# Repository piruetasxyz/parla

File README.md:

# parla

Un proyecto de piruetas, 2026.

## Módulos

Cada módulo tiene su propia carpeta con un proyecto de KiCad, organizado por versión y revisión (por ejemplo `parla-linea/parla-linea-v-0-rev-a/`).

|                      | parla-linea                            | parla-eurorack                           | parla-guitarra        | parla-estereo          |
| -------------------- | -------------------------------------- | ---------------------------------------- | --------------------- | ---------------------- |
| formato              | standalone                             | eurorack                                 | standalone            | standalone             |
| entrada alimentación | batería 9V                             | por definir                              | batería 9V            | por definir            |
| chip                 | PAM8403                                | por definir                              | LM386                 | PAM8403                |
| interfaz             | 1x pote                                | 2x potes                                 | 1x pote               | 2x potes               |
| entrada señal        | 1x línea TRS                           | 1x eurorack                              | 1x guitarra           | 1x línea TRS           |
| conector entrada     | TRS 1/8"                               | TS 1/8"                                  | TS 1/4"               | TRS 1/8"               |
| salidas              | 1x parlante, 1x línea                  | 1x parlante, 1x eurorack                 | 1x parlante           | 2x parlantes           |
| conector salida      | parlante: por definir, línea: TRS 1/8" | parlante: por definir, eurorack: TS 1/8" | parlante: por definir | parlantes: por definir |

### Extensores

|                  | parla-linea-extensor  | parla-eurorack-extensor |
| ---------------- | --------------------- | ----------------------- |
| formato          | standalone            | eurorack                |
| alimentación     | ninguna               | por definir             |
| chip             | ninguno               | por definir             |
| interfaz         | —                     | —                       |
| entradas         | 1x línea              | 1x eurorack             |
| conector entrada | TRS 1/8"              | TS 1/8"                 |
| salidas          | 1x parlante           | 1x parlante             |
| conector salida  | parlante: por definir | parlante: por definir   |

## Documentación

Esquemáticos, placas y bill of materials (BOM) de cada módulo, generados automáticamente: [docs](./docs/README.md).

### Agregar las bibliotecas de parla-linea a KiCad

Las bibliotecas generadas están en `parla-linea/parla-linea-v-0-rev-a/bibliotecas/`.
Para que KiCad las encuentre, abre primero el proyecto
`parla-linea/parla-linea-v-0-rev-a/parla-linea-v-0-rev-a.kicad_pro` y agrégalas
como bibliotecas específicas de ese proyecto:

1. En KiCad, abre **Preferencias → Administrar bibliotecas de símbolos…**.
2. En **Bibliotecas específicas del proyecto**, pulsa **Añadir biblioteca existente**
   y selecciona
   `parla-linea/parla-linea-v-0-rev-a/bibliotecas/parla-linea-v-0-rev-a.kicad_sym`.
3. Abre **Preferencias → Administrar bibliotecas de huellas…**.
4. En **Bibliotecas específicas del proyecto**, pulsa **Añadir biblioteca existente**
   y selecciona la carpeta
   `parla-linea/parla-linea-v-0-rev-a/bibliotecas/parla-linea-v-0-rev-a.pretty`
   (no un archivo dentro de ella).
5. Confirma los cambios. Las bibliotecas deberían aparecer en los selectores de
   símbolos y huellas del proyecto.

Agrégalas como bibliotecas **específicas del proyecto**, no globales, para que las
rutas queden asociadas a este proyecto. Los modelos 3D están en la carpeta hermana
`parla-linea/parla-linea-v-0-rev-a/bibliotecas/parla-linea-v-0-rev-a.3dshapes/`;
las huellas los referencian desde ahí, así que no hace falta registrarlos como
biblioteca aparte. Si el proyecto ya estaba abierto mientras agregabas las
bibliotecas, cierra y vuelve a abrir el proyecto.

### Enlaces por módulo

- parla-linea: [carpeta](https://github.com/piruetasxyz/parla/tree/main/parla-linea), [docs](./docs/parla-linea.md)
- parla-eurorack: [carpeta](https://github.com/piruetasxyz/parla/tree/main/parla-eurorack), [docs](./docs/parla-eurorack.md)
- parla-guitarra: [carpeta](https://github.com/piruetasxyz/parla/tree/main/parla-guitarra), [docs](./docs/parla-guitarra.md)
- parla-estereo: [carpeta](https://github.com/piruetasxyz/parla/tree/main/parla-estereo), [docs](./docs/parla-estereo.md)
- parla-linea-extensor: [carpeta](https://github.com/piruetasxyz/parla/tree/main/parla-linea-extensor), [docs](./docs/parla-linea-extensor.md)
- parla-eurorack-extensor: [carpeta](https://github.com/piruetasxyz/parla/tree/main/parla-eurorack-extensor), [docs](./docs/parla-eurorack-extensor.md)

## Versiones antiguas

Hicimos versiones preliminares que están en la carpeta [versiones-antiguas](https://github.com/piruetasxyz/parla/tree/main/versiones-antiguas):

- `parla-v0-borrador`: primeros experimentos de esquemáticos (enero-febrero 2026).
- `parla-v0-revA`: versión producida con SMD en JLCPCB.
- `parla-v0-revB`: revisión de la placa con algunos cambios (junio 2026), junto a sus gerbers y archivos de PCBA.
- `graficas`: logos y gráficas usadas en las placas.

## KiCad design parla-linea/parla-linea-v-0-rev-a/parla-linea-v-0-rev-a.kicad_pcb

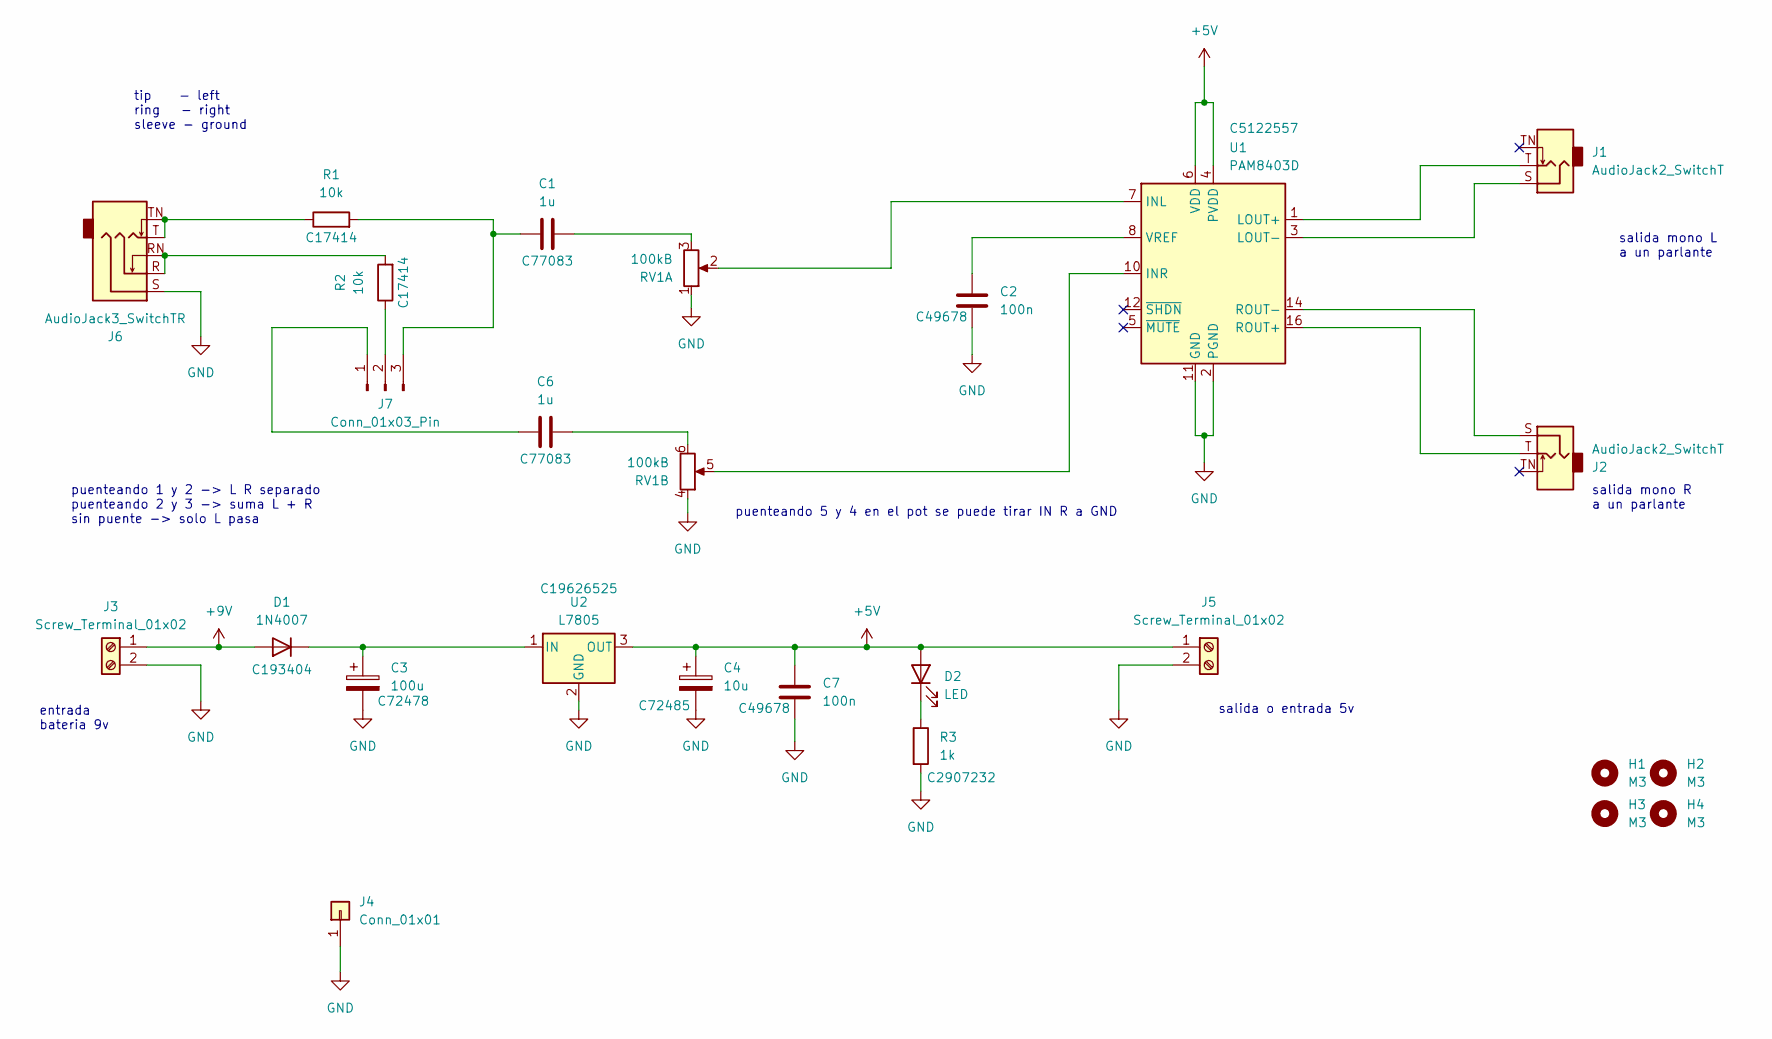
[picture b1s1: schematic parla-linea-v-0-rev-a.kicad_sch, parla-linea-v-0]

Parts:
C1, C6: 1u; C0805; LCSC C77083
C2, C7: 100n; C0805; LCSC C49678
C3: 100u; CAP-SMD_BD6.3-L6.6-W6.6-LS7.6-FD; LCSC C72478
C4: 10u; CAP-SMD_BD4.0-L4.3-W4.3-FD; LCSC C72485
D1: 1N4007; SOD-323_L1.8-W1.3-LS2.5-RD; LCSC C193404
D2: LED; LED3mm
H1, H2, H3, H4: M3; MountingHole_3.2mm_M3
J1, J2: AudioJack2_SwitchT; Jack_3.5mm_QingPu_WQP-PJ398SM_Vertical_CircularHoles
J3, J5: Screw_Terminal_01x02; TerminalBlock_MaiXu_MX126-5.0-02P_1x02_P5.00mm
J4: Conn_01x01; SolderWire-0.25sqmm_1x01_D0.65mm_OD1.7mm
J6: AudioJack3_SwitchTR; Jack_3.5mm_CUI_SJ1-3525N_Horizontal
J7: Conn_01x03_Pin; PinHeader_1x03_P2.54mm_Vertical
R1, R2: 10k; R0805; LCSC C17414
R3: 1k; R0805; LCSC C2907232
RV1: 100kB; Potentiometer_Alps_RK163_Dual_Horizontal
U1: PAM8403D; SOP-16_L10.0-W3.9-P1.27-LS6.0-BL; LCSC C5122557
U2: L7805; TO-252-2_L6.6-W6.1-P4.57-LS9.9-BR-CW; LCSC C19626525

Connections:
+5V: C4.1, C7.1, D2.2 (A), J5.1, U1.4 (PVDD), U1.6 (VDD), U1.13 (PVDD), U2.3 (OUT)
+9V: D1.2 (A), J3.1
GND: C2.2, C3.2, C4.2, C7.2, J3.2, J4.1 (Pin_1_1), J5.2, J6.S, R3.2, RV1.1, RV1.4, U1.2 (PGND), U1.11 (GND), U1.15 (PGND), U2.2 (GND)
unnamed: C1.2, RV1.3
unnamed: C6.2, RV1.6
unnamed: C3.1, D1.1 (K), U2.1 (IN)
unnamed: D2.1 (K), R3.1
unnamed: J6.R, J6.RN, R2.2
unnamed: J6.T, J6.TN, R1.1
unnamed: C6.1, J7.1
unnamed: J7.2, R2.1
unnamed: C1.1, J7.3, R1.2
unnamed: RV1.2, U1.7 (INL)
unnamed: RV1.5, U1.10 (INR)
unnamed: J1.T, U1.1 (LOUT+)
unnamed: J1.S, U1.3 (LOUT-)
unnamed: J2.T, U1.16 (ROUT+)
unnamed: J2.S, U1.14 (ROUT-)
unnamed: C2.1, U1.8 (VREF)

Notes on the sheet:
salida mono L a un parlante
tip - left ring - right sleeve - ground
salida mono R a un parlante
puenteando 1 y 2 -> L R separado puenteando 2 y 3 -> suma L + R sin puente -> solo L pasa
entrada bateria 9v
puenteando 5 y 4 en el pot se puede tirar IN R a GND
salida o entrada 5v

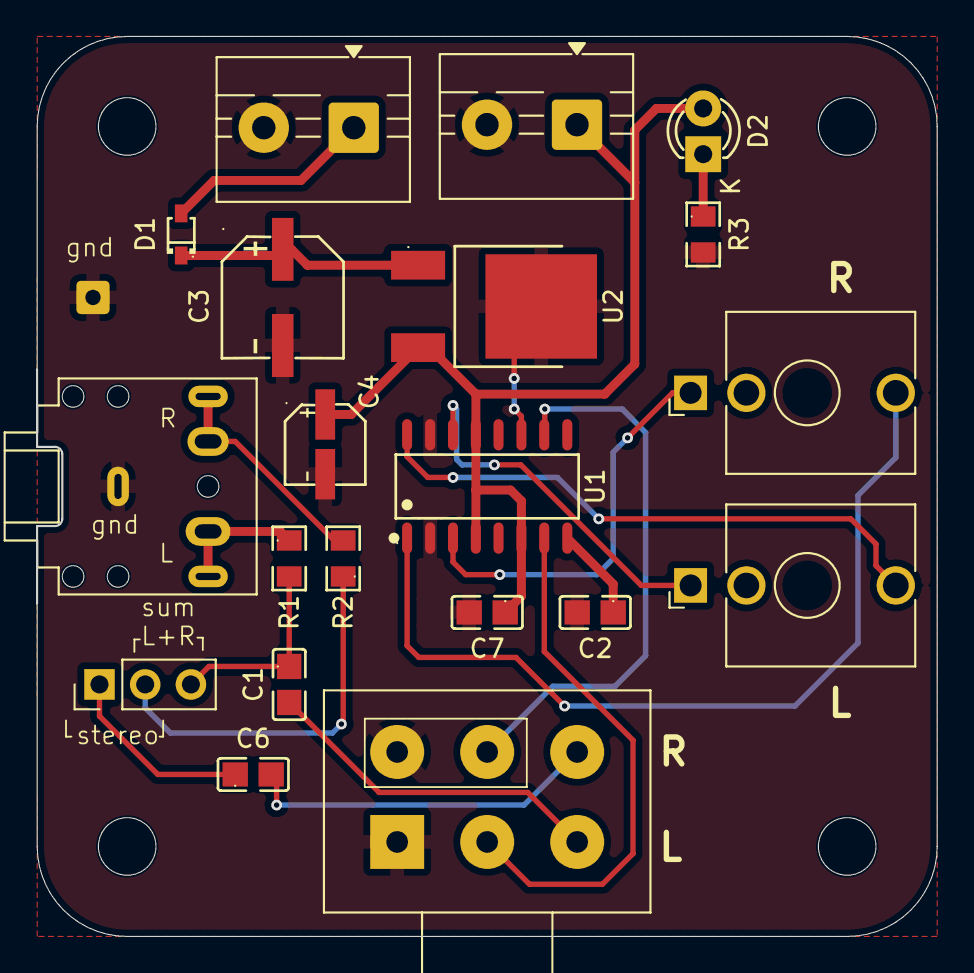
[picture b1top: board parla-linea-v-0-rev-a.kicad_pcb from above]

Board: 2 copper layers, 50.0 x 49.9 mm, 25 parts (0 on the bottom side), 19 nets.

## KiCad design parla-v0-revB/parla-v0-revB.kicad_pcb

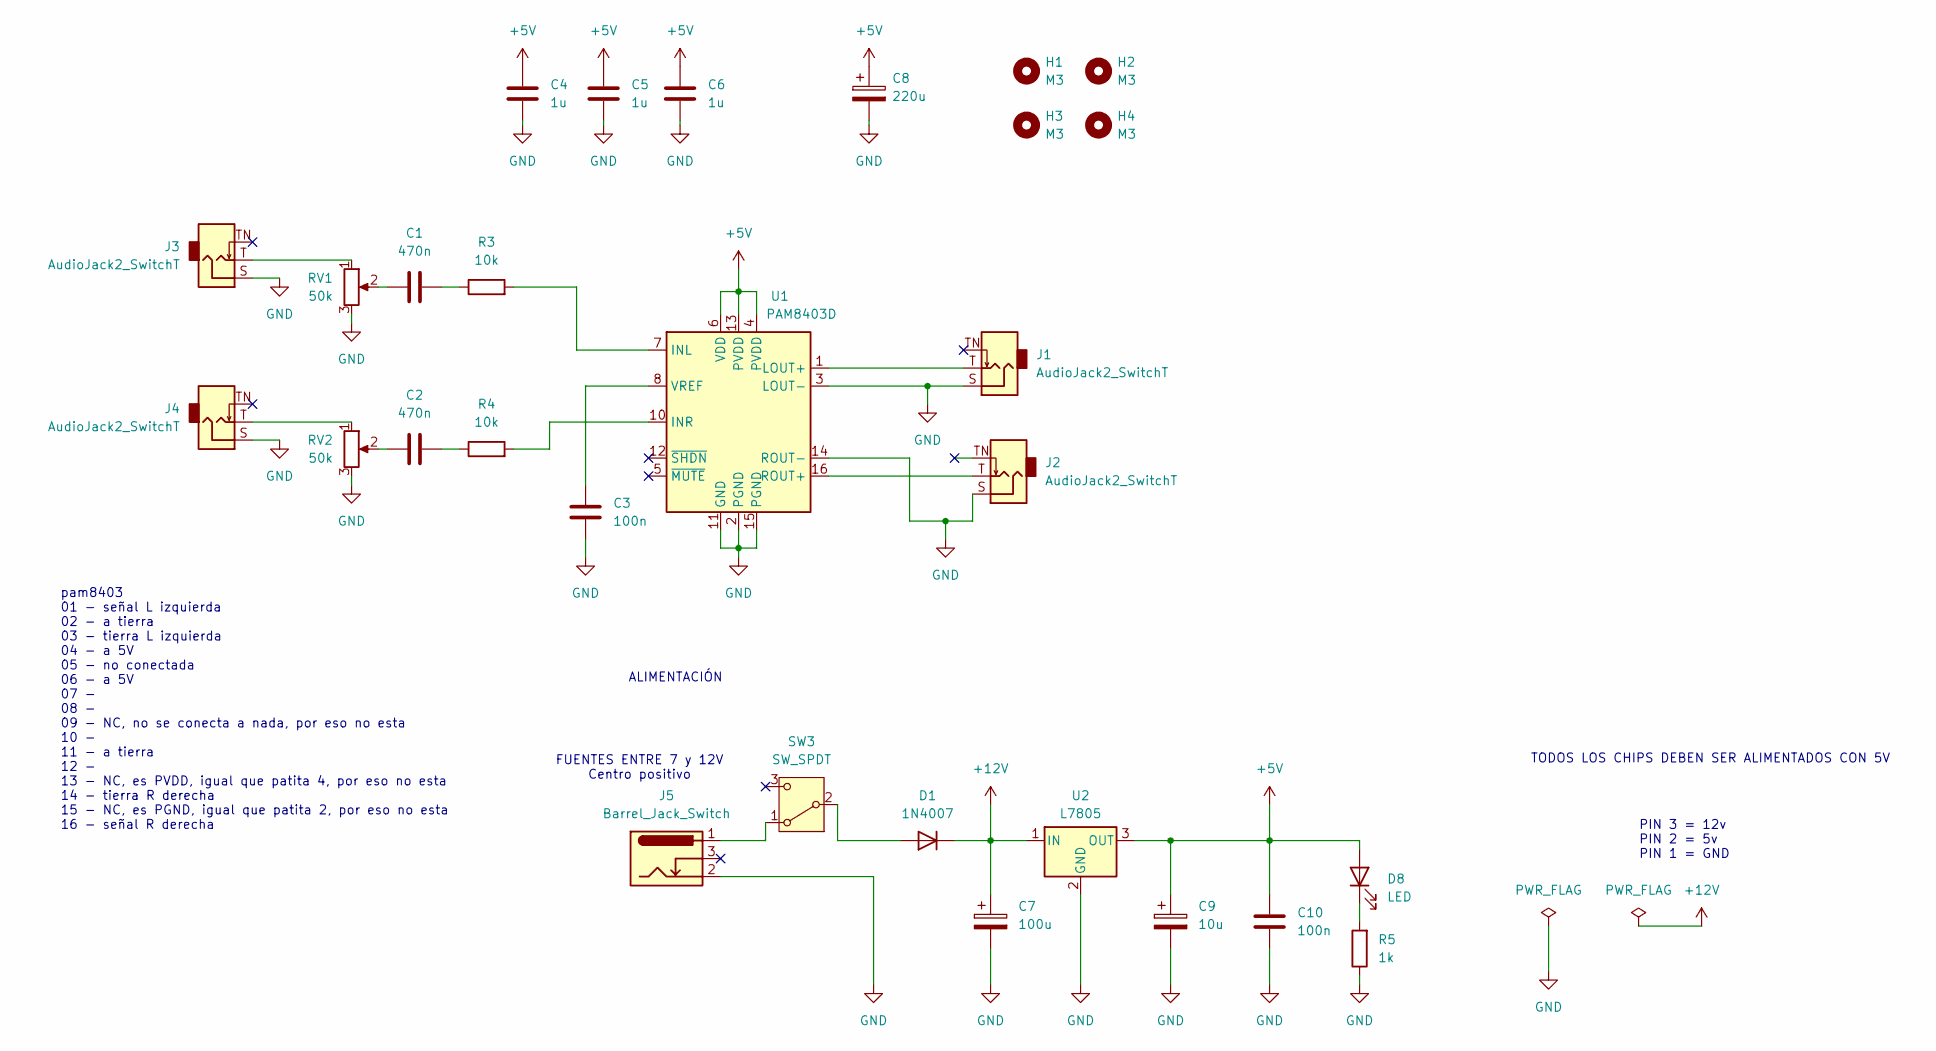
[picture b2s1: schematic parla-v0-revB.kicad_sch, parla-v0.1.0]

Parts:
C1, C2: 470n; C_Elec_4x5.4; LCSC C2895732
C3, C10: 100n; C_0805_2012Metric_Pad1.18x1.45mm_HandSolder; LCSC C49678
C4, C5, C6: 1u; C_0805_2012Metric_Pad1.18x1.45mm_HandSolder; LCSC C77083
C7: 100u; CP_Elec_5x5.4; LCSC C3347
C8: 220u; CP_Elec_6.3x7.7; LCSC C3342
C9: 10u; CP_Elec_4x5.4; LCSC C3357
D1: 1N4007; D_SOD-323_HandSoldering; LCSC C193404
D8: LED; LED_D5.0mm
H1, H2, H3, H4: M3; MountingHole_3.2mm_M3
J1, J2, J3, J4: AudioJack2_SwitchT; PJ301M-12-T_TN_S
J5: Barrel_Jack_Switch; BarrelJack_Horizontal
R3, R4: 10k; R_0805_2012Metric_Pad1.20x1.40mm_HandSolder; LCSC C17414
R5: 1k; R_0805_2012Metric_Pad1.20x1.40mm_HandSolder; LCSC C2907232
RV1, RV2: 50k; Potentiometer_Bourns_PTV09A-1_Single_Vertical
SW3: SW_SPDT; spdt_ssd12d00g3
U1: PAM8403D; SOP-16_4.4x10.4mm_P1.27mm; LCSC C5122557
U2: L7805; TO-252-2; LCSC C19626525

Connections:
+5V: C4.2, C5.2, C6.2, C8.1, C9.1, C10.1, D8.2 (A), U1.4 (PVDD), U1.6 (VDD), U1.13 (PVDD), U2.3 (OUT)
+12V: C7.1, D1.1 (K), U2.1 (IN)
GND: C3.2, C4.1, C5.1, C6.1, C7.2, C8.2, C9.2, C10.2, J1.S, J2.S, J3.S, J4.S, J5.2, R5.1, RV1.3, RV2.3, U1.2 (PGND), U1.3 (LOUT-), U1.11 (GND), U1.14 (ROUT-), U1.15 (PGND), U2.2 (GND)
unnamed: C1.1, RV1.2
unnamed: C1.2, R3.1
unnamed: C2.1, RV2.2
unnamed: C2.2, R4.1
unnamed: D1.2 (A), SW3.2 (B)
unnamed: D8.1 (K), R5.2
unnamed: J3.T, RV1.1
unnamed: J4.T, RV2.1
unnamed: J5.1, SW3.1 (A)
unnamed: R3.2, U1.7 (INL)
unnamed: R4.2, U1.10 (INR)
unnamed: J1.T, U1.1 (LOUT+)
unnamed: J2.T, U1.16 (ROUT+)
unnamed: C3.1, U1.8 (VREF)

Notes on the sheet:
FUENTES ENTRE 7 y 12V Centro positivo
PIN 3 = 12v PIN 2 = 5v PIN 1 = GND
TODOS LOS CHIPS DEBEN SER ALIMENTADOS CON 5V
ALIMENTACIÓN
pam8403 01 - señal L izquierda 02 - a tierra 03 - tierra L izquierda 04 - a 5V 05 - no conectada 06 - a 5V 07 - 08 - 09 - NC, no se conecta a nada, por eso no esta 10 - 11 - a tierra 12 - 13 - NC, es PVDD, igual que patita 4, por eso no esta 14 - tierra R derecha 15 - NC, es PGND, igual que patita 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

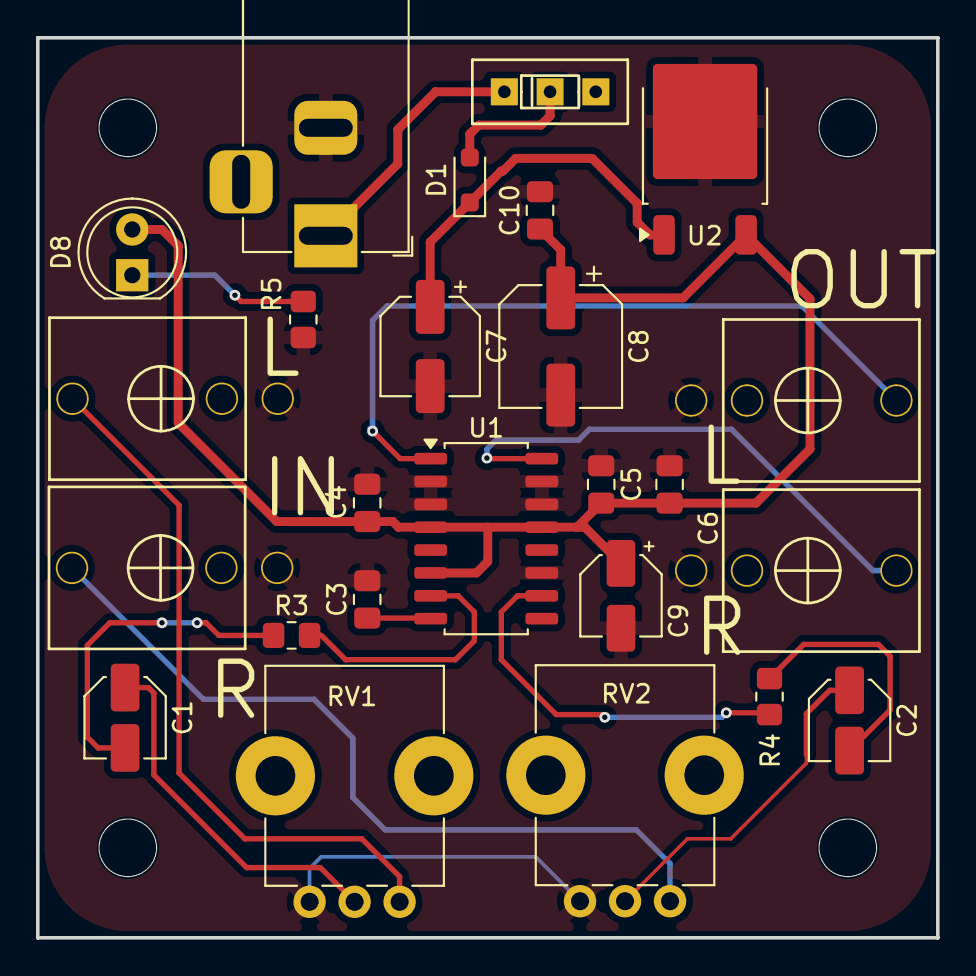
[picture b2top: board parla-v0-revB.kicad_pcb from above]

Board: 2 copper layers, 50.0 x 50.0 mm, 29 parts (0 on the bottom side), 17 nets.

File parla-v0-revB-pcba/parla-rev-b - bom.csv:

Comment,Designator,Footprint,LCSC Part Number
470n,"C1,C2",Capacitor_SMD:C_Elec_4x5.4,C2895732
100n,"C3,C10",Capacitor_SMD:C_0805_2012Metric_Pad1.18x1.45mm_HandSolder,C49678
1u,"C4,C5,C6",Capacitor_SMD:C_0805_2012Metric_Pad1.18x1.45mm_HandSolder,C77083
100u,C7,Capacitor_SMD:CP_Elec_6.3x7.7,C3347
220u,C8,Capacitor_SMD:CP_Elec_6.3x5.4,C3342
10u,C9,Capacitor_SMD:CP_Elec_4x5.4,C3357
1N4007,D1,Diode_SMD:D_SOD-323_HandSoldering,C193404
10k,"R3,R4",Resistor_SMD:R_0805_2012Metric_Pad1.20x1.40mm_HandSolder,C17414
1k,R5,Resistor_SMD:R_0805_2012Metric_Pad1.20x1.40mm_HandSolder,C2907232
PAM8403D,U1,Package_SO:SOP-16_4.4x10.4mm_P1.27mm,C5122557
L7805,U2,Package_TO_SOT_SMD:TO-252-2,C19626525

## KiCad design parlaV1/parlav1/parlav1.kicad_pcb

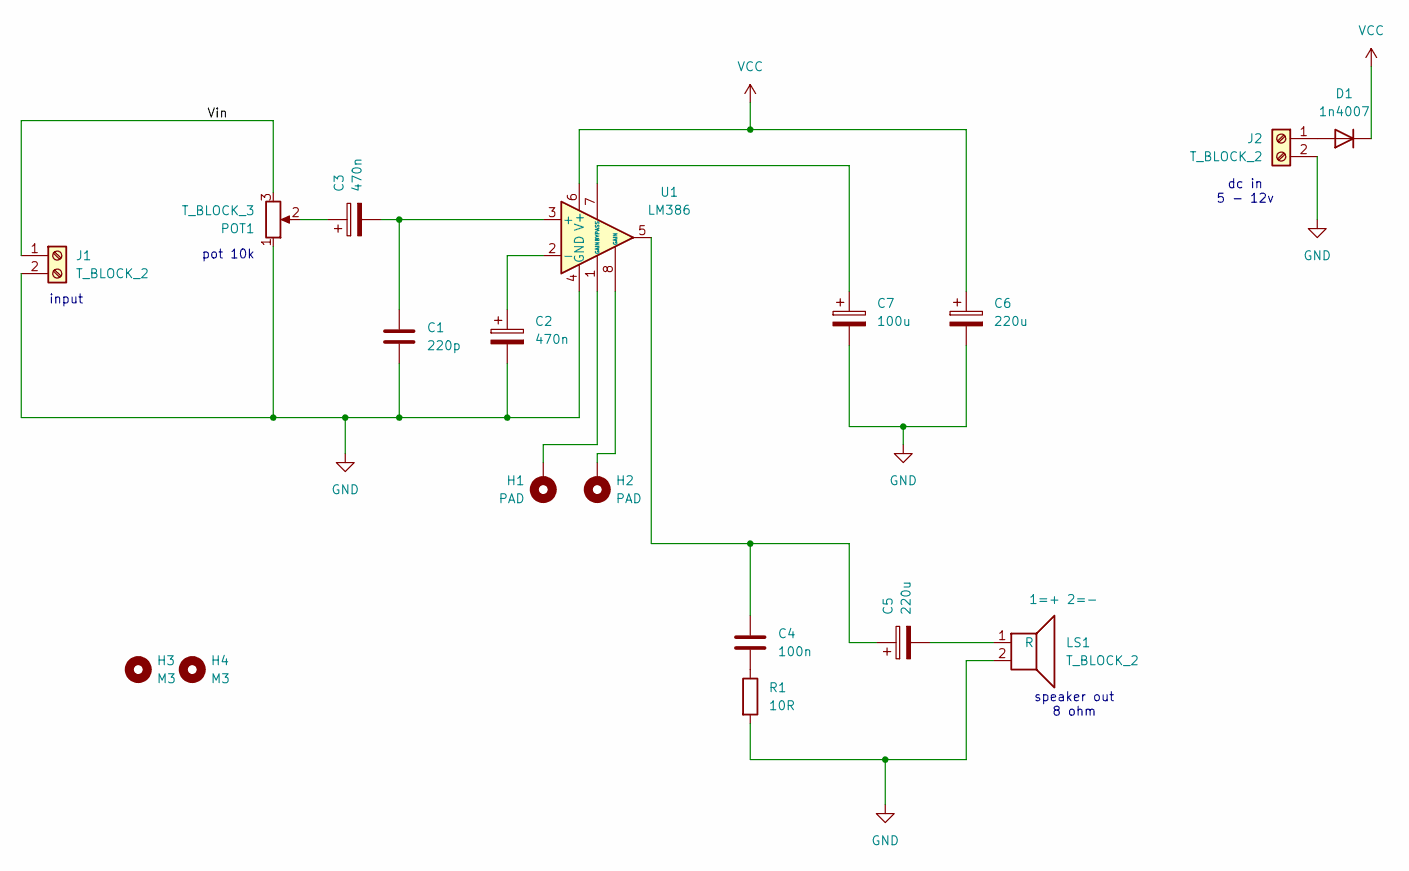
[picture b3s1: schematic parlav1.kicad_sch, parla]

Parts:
C1: 220p; C_0805_2012Metric; LCSC C107145
C2, C3: 470n; CP_Elec_4x5.4; LCSC C22387960
C4: 100n; C_0805_2012Metric; LCSC C49678
C5, C6: 220u; CP_Elec_6.3x5.4; LCSC C3345
C7: 100u; CP_Elec_5x5.4; LCSC C72473
D1: 1n4007; D_SOD-323; LCSC C193404
H1, H2: PAD; PinHeader_1x01_P2.54mm_Vertical
H3, H4: M3; MountingHole_3.2mm_M3
J1, J2: T_BLOCK_2; TerminalBlock_bornier-2_P5.08mm
LS1: T_BLOCK_2; TerminalBlock_bornier-2_P5.08mm
POT1: T_BLOCK_3; PinHeader_1x03_P2.54mm_Vertical
R1: 10R; R_0805_2012Metric; LCSC C2907296
U1: LM386; DIP-8_W7.62mm_LongPads

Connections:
/Vin: J1.1, POT1.3
GND: C1.2, C2.2, C6.2, C7.2, J1.2, J2.2, LS1.2, POT1.1, R1.2, U1.4 (GND)
unnamed: C3.1, POT1.2
unnamed: C4.1, C5.1, U1.5
unnamed: C4.2, R1.1
unnamed: C5.2, LS1.1
unnamed: D1.2 (A), J2.1
unnamed: H1.1, U1.1 (GAIN)
unnamed: H2.1, U1.8 (GAIN)
unnamed: C1.1, C3.2, U1.3 (+)
unnamed: C2.1, U1.2 (-)
unnamed: C7.1, U1.7 (BYPASS)
VCC: C6.1, D1.1 (K), U1.6 (V+)

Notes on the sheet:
speaker out 8 ohm
pot 10k
dc in 5 - 12v
input

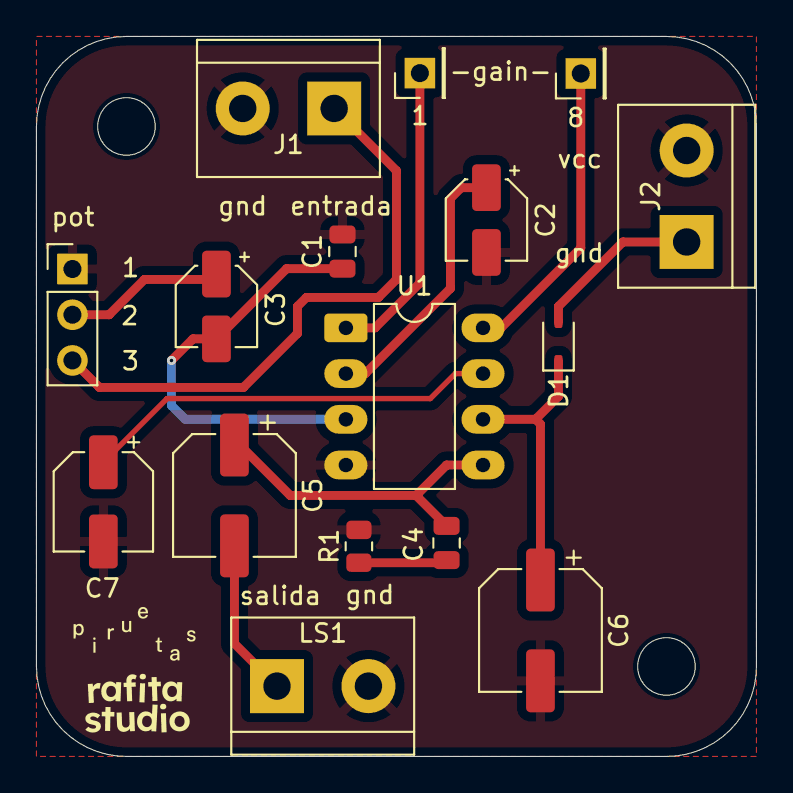
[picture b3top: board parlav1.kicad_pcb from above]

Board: 2 copper layers, 40.0 x 40.0 mm, 18 parts (0 on the bottom side), 13 nets.

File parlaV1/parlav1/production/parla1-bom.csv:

Comment,Designator,Footprint,LCSC Part Number
220p,C1,C_0805_2012Metric,C107145
470n,"C2,C3",CP_Elec_4x5.4,C22387960
100n,C4,C_0805_2012Metric,C49678
220u,"C5,C6",CP_Elec_6.3x5.4,C3345
100u,C7,CP_Elec_5x5.4,C72473
1n4007,D1,D_SOD-323,C193404
10R,R1,R_0805_2012Metric,C2907296

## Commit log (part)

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2026-01-15 agregar .gitignore y README
2026-01-15 agregar kicad a gitignore
2026-01-15 agregar carpeta de kicad v0
2026-01-16 agregar *.lck a .gitignore
2026-01-16 agregar borrador circuito
2026-01-16 agregar footprints
2026-01-16 agregar edgecuts
2026-01-16 agregar logo
2026-01-26 resetear pcb, agregar stereo
2026-01-26 agregar componentes ahora en SMD
2026-01-26 agregar nuevas graficas, falta wiring
2026-01-26 añadidos comentarios sch
2026-01-26 resueltos comentarios mati
2026-01-26 agregar nuevo ruteo
2026-01-27 agregar csv
2026-02-04 añadida parlaV1 by misaa
2026-06-02 borrar parla-stereo
2026-06-02 borrar subcarpeta history
2026-06-02 agregar .history/ a gitignore
2026-06-02 mover una carpeta arriba
2026-06-02 mover a revA
2026-06-06 subir reorden
2026-06-07 agregar vias
2026-06-23 agregar modificacion
2026-06-23 actualizada version smd
2026-06-23 nueva version matias
2026-06-23 agregar mis cambios
2026-06-23 editadas huellas standard
2026-06-23 borrar gerbers antiguos
2026-06-23 borrar csvs antiguos
2026-06-23 agregar archivos de produccion
